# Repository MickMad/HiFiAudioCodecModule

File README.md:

#HiFi Audio Codec Module
##A very small hifi audio codec module

The purpose of this project is to create a small (1 square inch board size) HiFi audio CODEC module to be used with I2S-compatible MCUs

More info here: 
https://hackaday.io/project/8567-hifi-audio-codec-module

The project is a submission for the following contest (The Square Inch project): 
https://hackaday.io/project/7813-the-square-inch-project

```
Copyright © Michele Perla 2015

This documentation describes Open Hardware and is licensed under the CERN OHL v. 1.2.
You may redistribute and modify this documentation under the terms of the CERN OHL v.1.2. 
(http://ohwr.org/cernohl). This documentation is distributed
WITHOUT ANY EXPRESS OR IMPLIED WARRANTY, INCLUDING OF
MERCHANTABILITY, SATISFACTORY QUALITY AND FITNESS FOR A
PARTICULAR PURPOSE. Please see the CERN OHL v.1.2 for applicable
conditions
```

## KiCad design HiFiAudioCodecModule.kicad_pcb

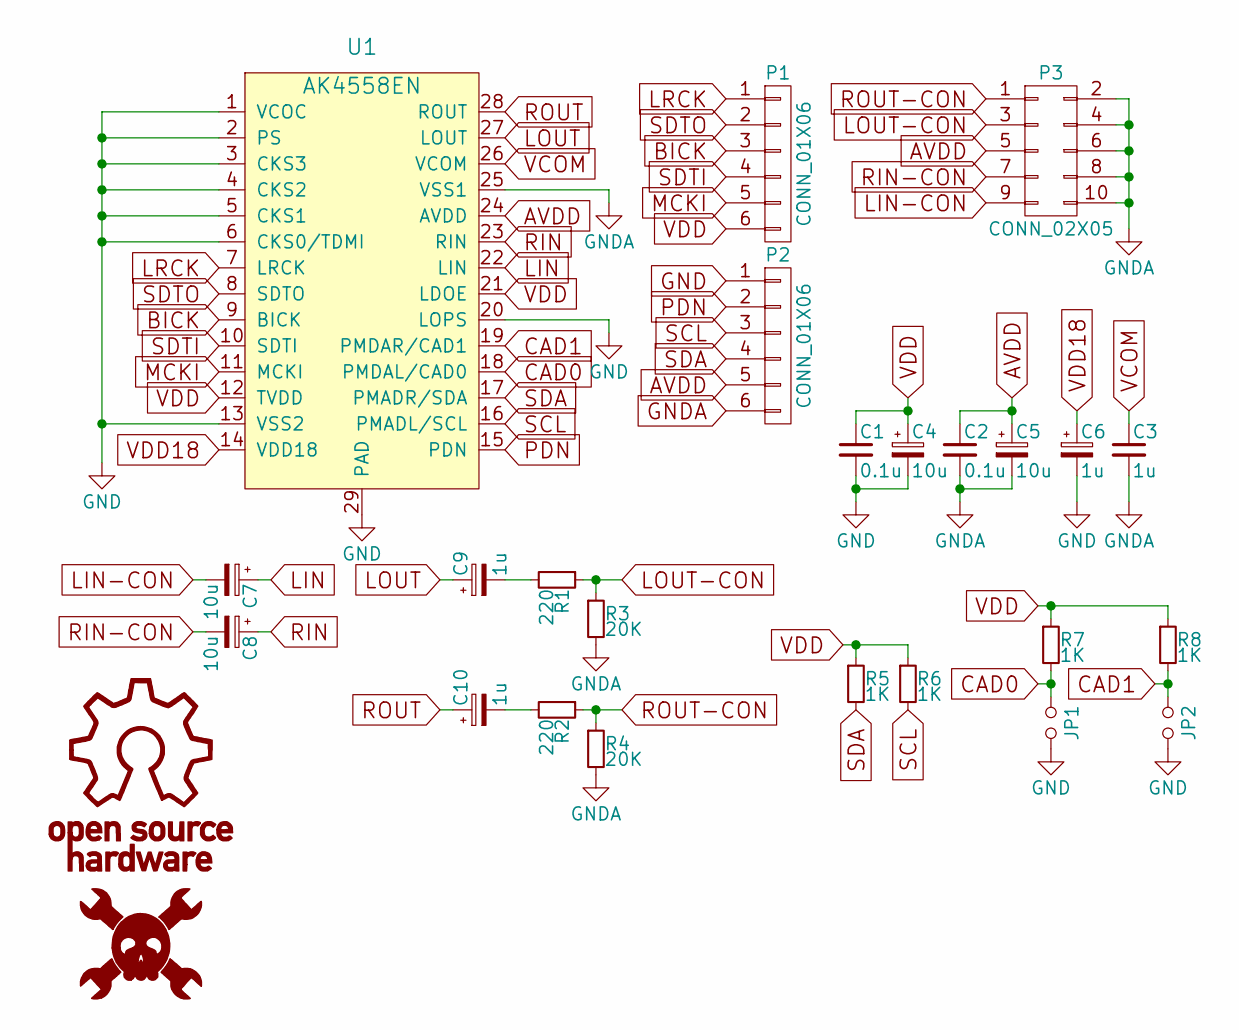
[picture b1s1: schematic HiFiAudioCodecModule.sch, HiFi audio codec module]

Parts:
C1, C2: 0.1u; C_0402
C3: 1u; C_0402
C4, C5, C7, C8: 10u; c_elec_4x5.3
C6, C9, C10: 1u; c_elec_3x5.3
JP1, JP2: Jumper_NO_Small; S_JUMPER_2
LOGO1: OSHW; LOGO
LOGO2: HACKADAY; LOGO
P1, P2: CONN_01X06; Pin_Header_Straight_1x06
P3: CONN_02X05; Pin_Header_Straight_2x05_mod
R1, R2: 220; R_0402
R3, R4: 20K; R_0402
R5, R6, R7, R8: 1K; R_0402
U1: AK4558EN; QFN-28-2xEP_5x5mm_Pitch0.5mm

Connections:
AVDD: C2.1, C5.1, P2.5, P3.5, U1.24 (AVDD)
BICK: P1.3, U1.9 (BICK)
CAD0: JP1.1, R7.2, U1.18 (PMDAL/CAD0)
CAD1: JP2.1, R8.2, U1.19 (PMDAR/CAD1)
GND: C1.2, C4.2, C6.2, JP1.2, JP2.2, P2.1, U1.1 (VCOC), U1.2 (PS), U1.3 (CKS3), U1.4 (CKS2), U1.5 (CKS1), U1.6 (CKS0/TDMI), U1.13 (VSS2), U1.20 (LOPS), U1.29 (PAD)
GNDA: C2.2, C3.2, C5.2, P2.6, P3.2, P3.4, P3.6, P3.8, P3.10, R3.2, R4.2, U1.25 (VSS1)
LIN: C7.1, U1.22 (LIN)
LIN-CON: C7.2, P3.9
LOUT: C9.1, U1.27 (LOUT)
LOUT-CON: P3.3, R1.1, R3.1
LRCK: P1.1, U1.7 (LRCK)
MCKI: P1.5, U1.11 (MCKI)
unnamed: C9.2, R1.2
unnamed: C10.2, R2.2
PDN: P2.2, U1.15 (PDN)
RIN: C8.1, U1.23 (RIN)
RIN-CON: C8.2, P3.7
ROUT: C10.1, U1.28 (ROUT)
ROUT-CON: P3.1, R2.1, R4.1
SCL: P2.3, R6.2, U1.16 (PMADL/SCL)
SDA: P2.4, R5.2, U1.17 (PMADR/SDA)
SDTI: P1.4, U1.10 (SDTI)
SDTO: P1.2, U1.8 (SDTO)
VCOM: C3.1, U1.26 (VCOM)
VDD: C1.1, C4.1, P1.6, R5.1, R6.1, R7.1, R8.1, U1.12 (TVDD), U1.21 (LDOE)
VDD18: C6.1, U1.14 (VDD18)

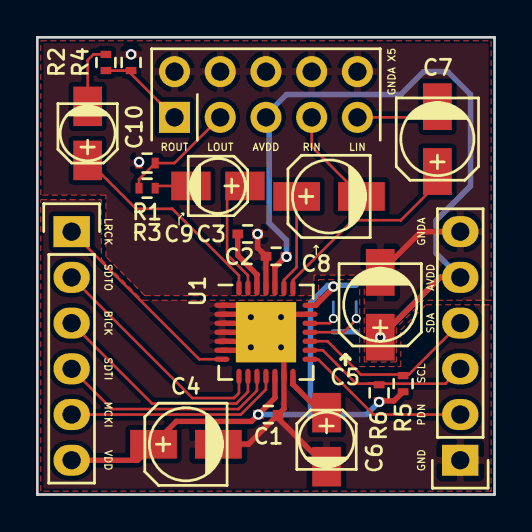
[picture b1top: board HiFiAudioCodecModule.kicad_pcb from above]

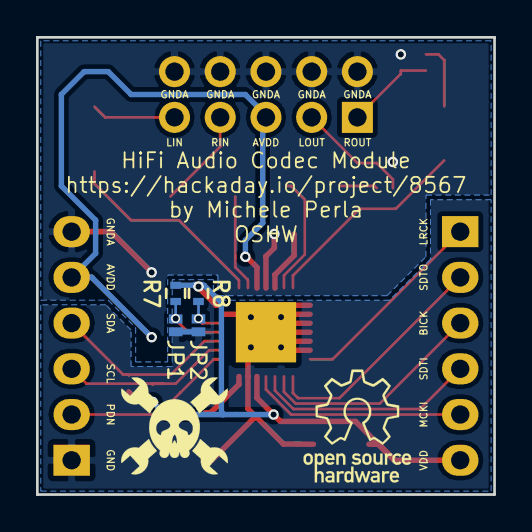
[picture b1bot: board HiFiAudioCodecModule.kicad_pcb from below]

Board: 2 copper layers, 25.4 x 25.4 mm, 26 parts (6 on the bottom side), 26 nets.

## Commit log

2015-12-08 :space_invader: Added .gitattributes
2015-12-08 First commit
    Pushed all files to github in order to be compliant with the Square Inch
    Project rules
2015-12-08 Revised PCB page layout
    Revised PCB page layout
2015-12-09 Moved graphics to "graphics" subfolder
    Moved graphics to "graphics" subfolder
2016-01-12 Added manf#s in schematic, fixed footprints, preparing rev.2
    Preparing rev.2 layout:
    -added manf# to check prices for manufacture w/ KiCost
    -changed in/out decoupling caps to thru-hole bipolar audio caps
    (Nichicon)
    -reduced real estate requirements for bypass caps (all 3 mm dia. caps)
    NOTE:LAYOUT COMPROMISED, STILL NEEDS TO BE FIXED
